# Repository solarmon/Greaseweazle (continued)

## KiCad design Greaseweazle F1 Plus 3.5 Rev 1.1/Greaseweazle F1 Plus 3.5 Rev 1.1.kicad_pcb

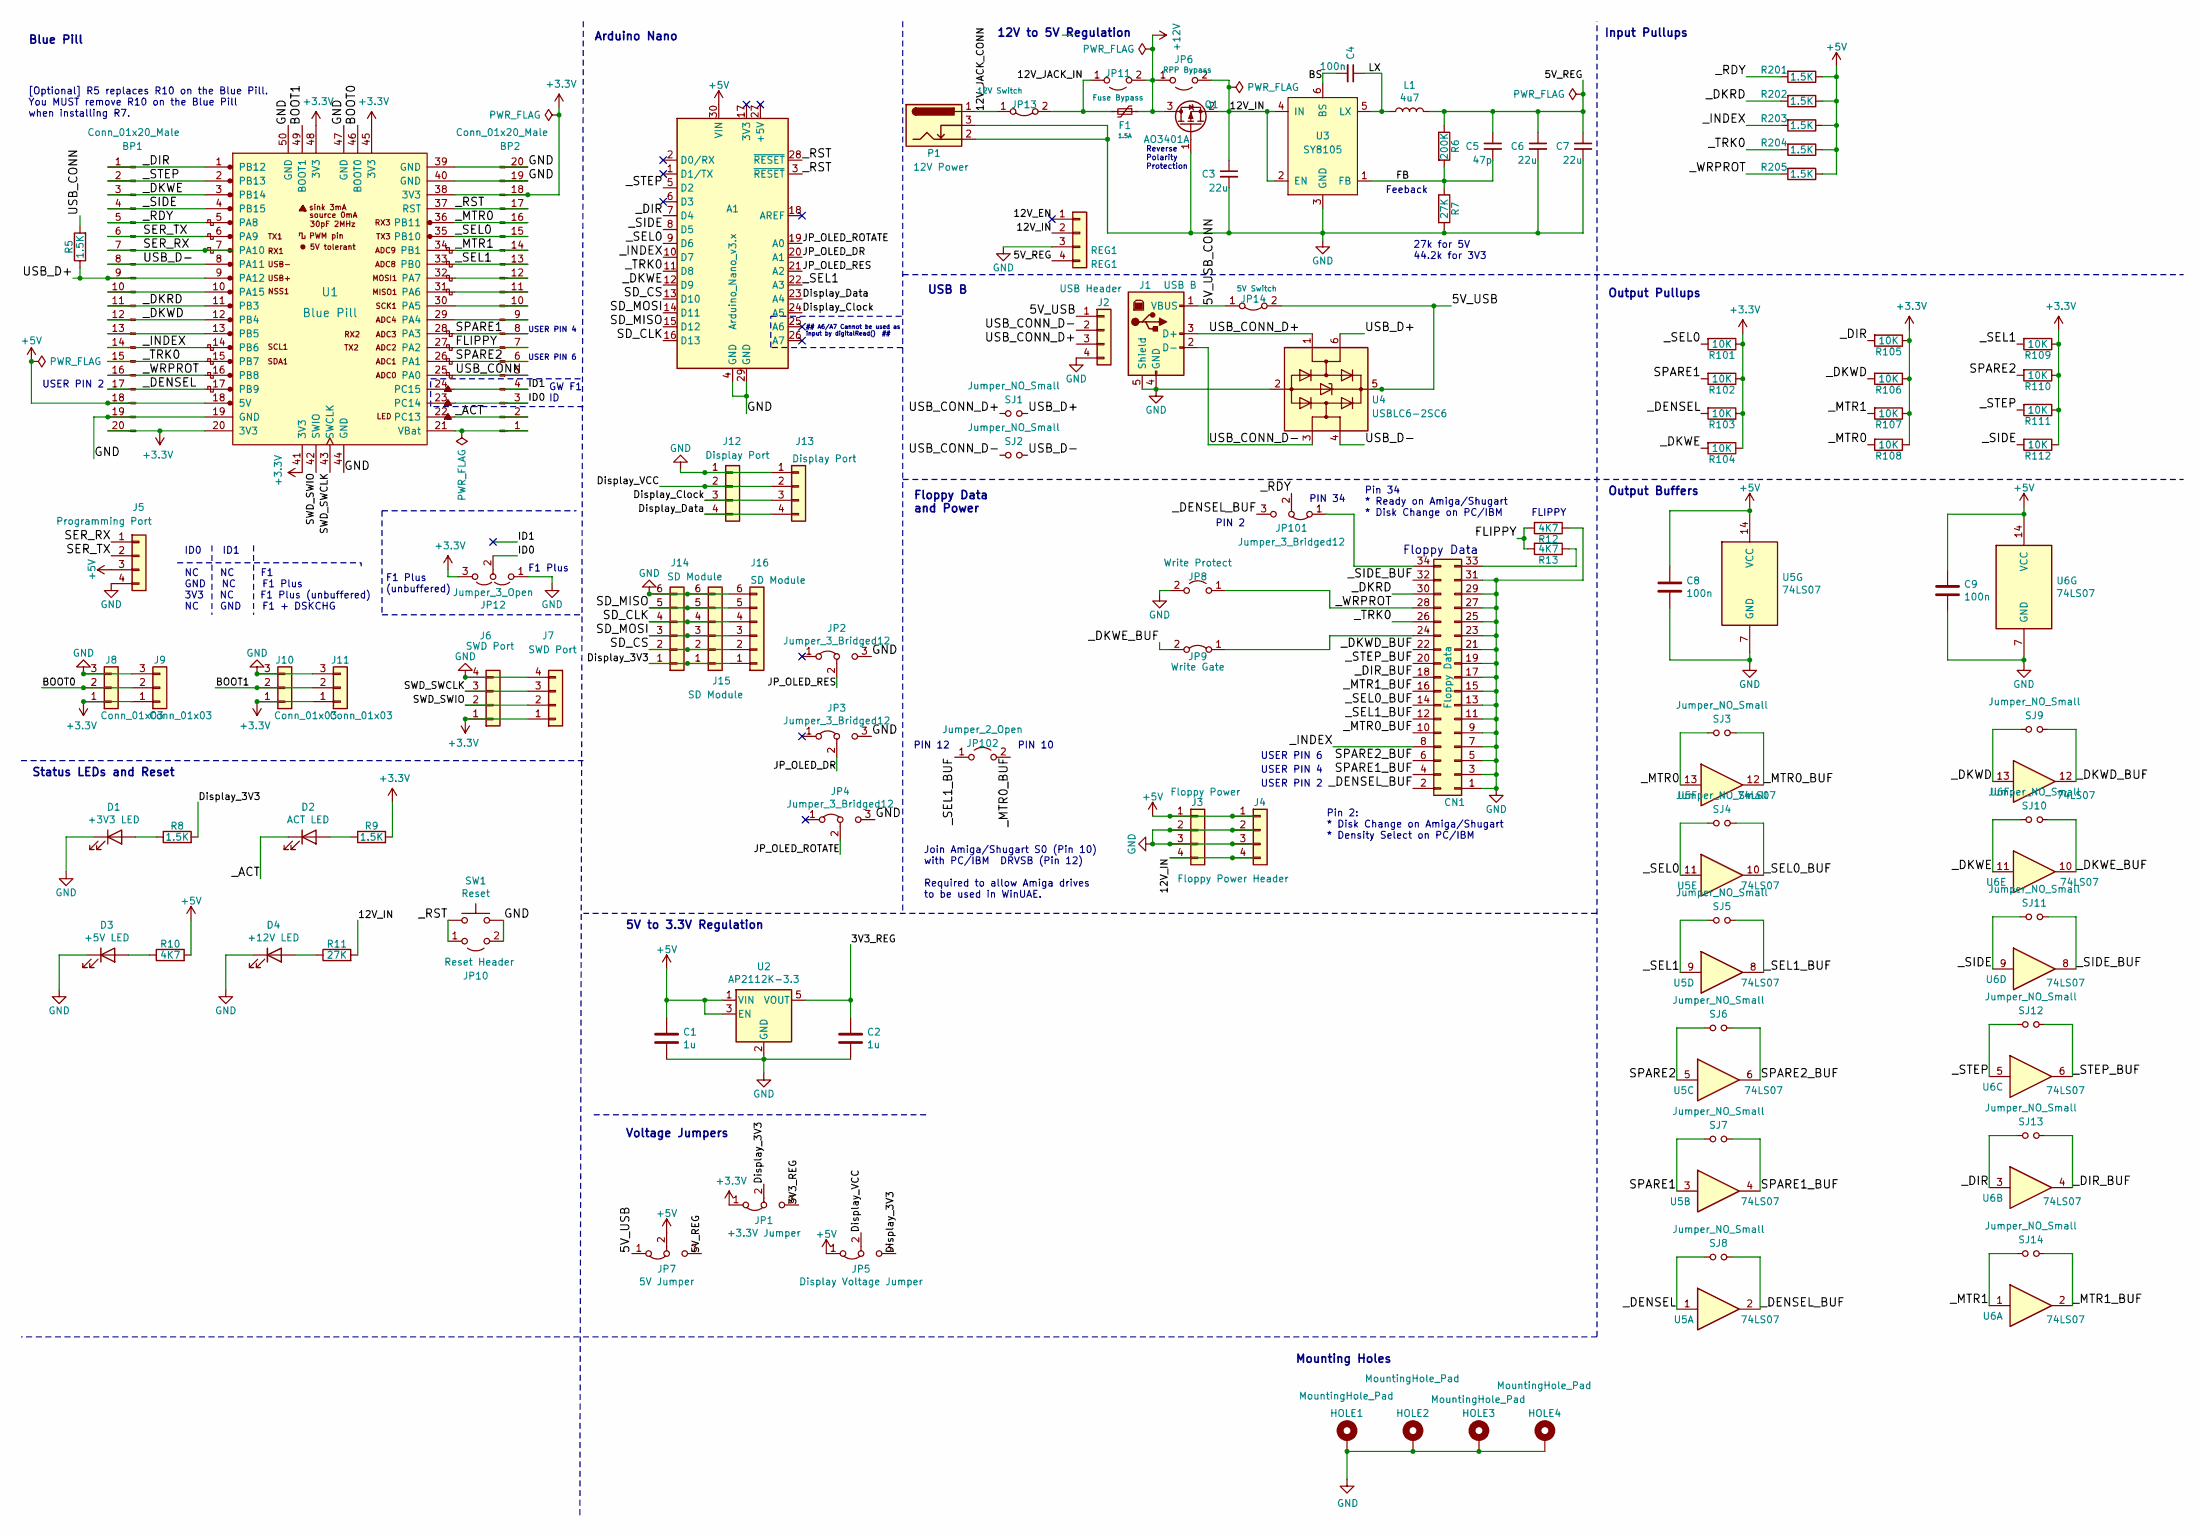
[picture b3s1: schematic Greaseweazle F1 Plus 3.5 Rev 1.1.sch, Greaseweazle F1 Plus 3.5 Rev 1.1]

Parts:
A1: Arduino_Nano_v3.x; Arduino_Nano
BP1, BP2: Conn_01x20_Male; PinHeader_1x20_P2.54mm_Vertical
C1, C2: 1u; C_0805_2012Metric_Pad1.15x1.40mm_HandSolder
C3, C6, C7: 22u; C_0805_2012Metric_Pad1.15x1.40mm_HandSolder
C4, C8, C9: 100n; C_0805_2012Metric_Pad1.15x1.40mm_HandSolder
C5: 47p; C_0805_2012Metric_Pad1.15x1.40mm_HandSolder
CN1: Floppy Data; PinHeader_2x17_P2.54mm_Vertical
D1: +3V3 LED; LED_0805_2012Metric_Pad1.15x1.40mm_HandSolder
D2: ACT LED; LED_0805_2012Metric_Pad1.15x1.40mm_HandSolder
D3: +5V LED; LED_0805_2012Metric_Pad1.15x1.40mm_HandSolder
D4: +12V LED; LED_0805_2012Metric_Pad1.15x1.40mm_HandSolder
F1: 1.5A; Fuse_1206_3216Metric_Pad1.42x1.75mm_HandSolder; LCSC C371166
HOLE1, HOLE2, HOLE3, HOLE4: MountingHole_Pad; HOLE_3MM
J1: USB B; conn_usb_B; LCSC C498173
J2: USB Header; PinHeader_1x04_P2.54mm_Vertical
J3: Floppy Power; PinHeader_1x04_P2.54mm_Horizontal
J4: Floppy Power Header; PinHeader_1x04_P2.54mm_Vertical
J5: Programming Port; PinHeader_1x04_P2.54mm_Horizontal
J6, J7: SWD Port; PinHeader_1x04_P2.54mm_Horizontal
J8, J9, J10, J11: Conn_01x03; PinHeader_1x03_P2.54mm_Horizontal
J12, J13: Display Port; PinHeader_1x04_P2.54mm_Vertical
J14, J15, J16: SD Module; SD_Micro_Module_Upside_Down
JP1: +3.3V Jumper; PinHeader_1x03_P2.54mm_Vertical
JP2, JP3, JP4: Jumper_3_Bridged12; PinHeader_1x03_P2.54mm_Vertical
JP5: Display Voltage Jumper; PinHeader_1x03_P2.54mm_Vertical
JP6: RPP Bypass; PinHeader_1x02_P2.54mm_Vertical
JP7: 5V Jumper; PinHeader_1x03_P2.54mm_Vertical
JP8: Write Protect; PinHeader_1x02_P2.54mm_Horizontal
JP9: Write Gate; PinHeader_1x02_P2.54mm_Horizontal
JP10: Reset Header; PinHeader_1x02_P2.54mm_Vertical
JP11: Fuse Bypass; PinHeader_1x02_P2.54mm_Vertical
JP12: Jumper_3_Open; SolderJumper-3_P1.3mm_Open_RoundedPad1.0x1.5mm
JP13: 12V Switch; PinHeader_1x02_P2.54mm_Vertical
JP14: 5V Switch; PinHeader_1x02_P2.54mm_Vertical
JP101: Jumper_3_Bridged12; PinHeader_1x03_P2.54mm_Horizontal
JP102: Jumper_2_Open; PinHeader_1x02_P2.54mm_Vertical
L1: 4u7; MWSA0503S
P1: 12V Power; BarrelJack_Horizontal; LCSC C16214
Q1: AO3401A; SOT-23_Handsoldering; LCSC C15127
R5, R8, R9, R201, R202, R203, R204, R205: 1.5K; R_0805_2012Metric_Pad1.15x1.40mm_HandSolder
R6: 200K; R_0805_2012Metric_Pad1.15x1.40mm_HandSolder
R7, R11: 27K; R_0805_2012Metric_Pad1.15x1.40mm_HandSolder
R10, R12, R13: 4K7; R_0805_2012Metric_Pad1.15x1.40mm_HandSolder
R101, R102, R103, R104, R105, R106, R107, R108, R109, R110, R111, R112: 10K; R_0805_2012Metric_Pad1.15x1.40mm_HandSolder
REG1: REG1; PinHeader_1x04_P2.54mm_Vertical
SJ1, SJ2, SJ3, SJ4, SJ5, SJ6, SJ7, SJ8, SJ9, SJ10, SJ11, SJ12, SJ13, SJ14: Jumper_NO_Small; SolderJumper-2_Open_RoundedPad0.5x1.0mm
SW1: Reset; PUSH_BUTTON_RIGHT_ANGLE
U1: Blue Pill; YAAJ_BluePill_SWD_1_BootPins
U2: AP2112K-3.3; SOT-23-5_HandSoldering; LCSC C51118
U3: SY8105; TSOT-23-6_HandSoldering; LCSC C178247
U4: USBLC6-2SC6; SOT-23-6_Handsoldering; LCSC C7519
U5, U6: 74LS07; SOIC-14_3.9x8.7mm_P1.27mm; LCSC C513513

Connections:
+3V3: BP1.20, BP2.18, J6.1, J7.1, J8.1, J9.1, J10.1, J11.1, JP1.1 (A), JP12.3 (B), R9.2, R101.1, R102.1, R103.1, R104.1, R105.1, R106.1, R107.1, R108.1, R109.1, R110.1, R111.1, R112.1, U1.20 (3V3), U1.38 (3V3), U1.41 (3V3), U1.45 (3V3), U1.48 (3V3); also elsewhere on the board
+5V: A1.30 (VIN), BP1.18, C1.1, C8.1, C9.1, J3.1, J4.1, J5.3, JP5.1 (A), JP7.2 (C), R10.2, R201.1, R202.1, R203.1, R204.1, R205.1, U1.18 (5V), U2.1 (VIN), U2.3 (EN), U5.14 (VCC), U6.14 (VCC); also elsewhere on the board
+12V: F1.1, JP6.1 (A), JP11.2 (B), Q1.3 (D)
/3V3_REG: C2.1, JP1.3 (B), U2.5 (VOUT)
/5V_REG: C5.1, C6.1, C7.1, JP7.3 (B), L1.2, R6.1, REG1.4
/5V_USB: J2.1, JP7.1 (A), JP14.2 (B), U4.5 (VBUS)
/5V_USB_CONN: J1.1 (VBUS), JP14.1 (A)
/12V_EN: REG1.1
/12V_IN: C3.1, J3.4, J4.4, JP6.2 (B), Q1.2 (S), R11.2, REG1.2, U3.2 (EN), U3.4 (IN); also elsewhere on the board
/12V_JACK_CONN: JP13.1 (A), P1.1
/12V_JACK_IN: F1.2, JP11.1 (A), JP13.2 (B)
/BOOT0: J8.2, J9.2, U1.46 (BOOT0)
/BOOT1: J10.2, J11.2, U1.49 (BOOT1)
/BS: C4.2, U3.6 (BS)
/Display_3V3: J14.1, J15.1, J16.1, JP1.2 (C), JP5.3 (B), R8.2; also elsewhere on the board
/Display_Clock: A1.24 (A5), J12.3, J13.3
/Display_Data: A1.23 (A4), J12.4, J13.4
/Display_VCC: J12.2, J13.2, JP5.2 (C)
/FB: C5.2, R6.2, R7.1, U3.1 (FB)
/FLIPPY: BP2.7, R12.2, R13.2, U1.27 (PA2)
/ID0: BP2.3, JP12.2 (C), U1.23 (PC14)
/ID1: BP2.4, U1.24 (PC15)
/JP_OLED_DR: A1.20 (A1), JP3.2 (C)
/JP_OLED_RES: A1.21 (A2), JP2.2 (C)
/JP_OLED_ROTATE: A1.19 (A0), JP4.2 (C)
/LX: C4.1, L1.1, U3.5 (LX)
/SD_CLK: A1.16 (D13), J14.4, J15.4, J16.4
/SD_CS: A1.13 (D10), J14.2, J15.2, J16.2
/SD_MISO: A1.15 (D12), J14.5, J15.5, J16.5
/SD_MOSI: A1.14 (D11), J14.3, J15.3, J16.3
/SER_RX: BP1.7, J5.1, U1.7 (PA10)
/SER_TX: BP1.6, J5.2, U1.6 (PA9)
/SPARE1: BP2.8, R102.2, SJ7.2, U1.28 (PA3), U5.3
/SPARE1_BUF: CN1.4, SJ7.1, U5.4
/SPARE2: BP2.6, R110.2, SJ6.2, U1.26 (PA1), U5.5
/SPARE2_BUF: CN1.6, SJ6.1, U5.6
/SWD_SWCLK: J6.3, J7.3, U1.43 (SWCLK)
/SWD_SWIO: J6.2, J7.2, U1.42 (SWIO)
/USB_CONN: BP2.5, R5.2, U1.25 (PA0); also elsewhere on the board
/USB_CONN_D+: J1.3 (D+), J2.3, SJ1.2, U4.1 (I/O1)
/USB_CONN_D-: J1.2 (D-), J2.2, SJ2.2, U4.3 (I/O2)
/USB_D+: BP1.9, R5.1, SJ1.1, U1.9 (PA12), U4.6 (I/O1); also elsewhere on the board
/USB_D-: BP1.8, SJ2.1, U1.8 (PA11), U4.4 (I/O2)
/_ACT: BP2.2, D2.1 (K), U1.22 (PC13); also elsewhere on the board
/_DENSEL: BP1.17, R103.2, SJ8.2, U1.17 (PB9), U5.1
/_DENSEL_BUF: CN1.2, JP101.3 (B), SJ8.1, U5.2
/_DIR: A1.7 (D4), BP1.1, R105.2, SJ13.2, U1.1 (PB12), U6.3
/_DIR_BUF: CN1.18, SJ13.1, U6.4
/_DKRD: BP1.11, CN1.30, R202.2, U1.11 (PB3)
/_DKWD: BP1.12, R106.2, SJ9.2, U1.12 (PB4), U6.13
/_DKWD_BUF: CN1.22, SJ9.1, U6.12
/_DKWE: A1.12 (D9), BP1.3, R104.2, SJ10.2, U1.3 (PB14), U6.11
/_DKWE_BUF: JP9.2 (B), SJ10.1, U6.10
/_INDEX: A1.10 (D7), BP1.14, CN1.8, R203.2, U1.14 (PB6)
/_MTR0: BP2.16, R108.2, SJ3.2, U1.36 (PB11), U5.13
/_MTR0_BUF: CN1.10, JP102.2 (B), SJ3.1, U5.12
/_MTR1: BP2.14, R107.2, SJ14.2, U1.34 (PB1), U6.1
/_MTR1_BUF: CN1.16, SJ14.1, U6.2
/_RDY: BP1.5, JP101.2 (C), R201.2, U1.5 (PA8)
/_RST: A1.3 (~RESET), A1.28 (~RESET), BP2.17, JP10.1 (A), SW1.1, U1.37 (RST)
/_SEL0: A1.9 (D6), BP2.15, R101.2, SJ4.2, U1.35 (PB10), U5.11
/_SEL0_BUF: CN1.14, SJ4.1, U5.10
/_SEL1: A1.22 (A3), BP2.13, R109.2, SJ5.2, U1.33 (PB0), U5.9
/_SEL1_BUF: CN1.12, JP102.1 (A), SJ5.1, U5.8
/_SIDE: A1.8 (D5), BP1.4, R112.2, SJ11.2, U1.4 (PB15), U6.9
/_SIDE_BUF: CN1.32, SJ11.1, U6.8
/_STEP: A1.5 (D2), BP1.2, R111.2, SJ12.2, U1.2 (PB13), U6.5
/_STEP_BUF: CN1.20, SJ12.1, U6.6
/_TRK0: A1.11 (D8), BP1.15, CN1.26, R204.2, U1.15 (PB7)
/_WRPROT: BP1.16, CN1.28, JP8.1 (A), R205.2, U1.16 (PB8)
GND: A1.4 (GND), A1.29 (GND), BP1.19, BP2.19, BP2.20, C1.2, C2.2, C3.2, C6.2, C7.2, C8.2, C9.2, CN1.1, CN1.3, CN1.5, CN1.7, CN1.9, CN1.11, CN1.13, CN1.15, CN1.17, CN1.19, CN1.21, CN1.23, CN1.25, CN1.27, CN1.29, CN1.31, D1.1 (K), D3.1 (K), D4.1 (K), HOLE1.1, HOLE2.1, HOLE3.1, HOLE4.1, J1.4 (GND), J1.5 (Shield), J2.4, J3.2, J3.3, J4.2, J4.3, J5.4, J6.4, J7.4, J8.3, J9.3, J10.3, J11.3, J12.1, J13.1, J14.6, J15.6, J16.6, JP2.3 (B), JP3.3 (B), JP4.3 (B), JP8.2 (B), JP10.2 (B), JP12.1 (A), P1.2, P1.3, Q1.1 (G), R7.2, R12.1, REG1.3, SW1.2, U1.19 (GND), U1.39 (GND), U1.40 (GND), U1.44 (GND), U1.47 (GND), U1.50 (GND), U2.2 (GND), U3.3 (GND), U4.2 (GND), U5.7 (GND), U6.7 (GND); also elsewhere on the board
unnamed: BP1.10, U1.10 (PA15)
unnamed: BP1.13, U1.13 (PB5)
unnamed: BP2.1, U1.21 (VBat)
unnamed: BP2.9, U1.29 (PA4)
unnamed: BP2.10, U1.30 (PA5)
unnamed: BP2.11, U1.31 (PA6)
unnamed: BP2.12, U1.32 (PA7)
unnamed: CN1.24, JP9.1 (A)
unnamed: CN1.33, R13.1
unnamed: CN1.34, JP101.1 (A)
unnamed 89: D1.2 (A), R8.1; also elsewhere on the board
unnamed 90: D2.2 (A), R9.1; also elsewhere on the board
unnamed 91: D3.2 (A), R10.1; also elsewhere on the board
unnamed 92: D4.2 (A), R11.1; also elsewhere on the board

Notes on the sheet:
Floppy Data
[Optional] R5 replaces R10 on the Blue Pill. You MUST remove R10 on the Blue Pill when installing R7.
Feeback
27k for 5V 44.2k for 3V3
Reverse Polarity Protection
12V to 5V Regulation
5V to 3.3V Regulation
Floppy Data and Power
Blue Pill
Arduino Nano
Voltage Jumpers
USB B
Mounting Holes
Status LEDs and Reset
GW F1 ID
F1 Plus
FLIPPY
Input Pullups
Output Pullups
Output Buffers
USER PIN 2
USER PIN 4
USER PIN 6
## A6/A7 Cannot be used as input by digitalRead() ##
Join Amiga/Shugart S0 (Pin 10) with PC/IBM DRVSB (Pin 12) Required to allow Amiga drives to be used in WinUAE.
PIN 12
PIN 10
PIN 34
PIN 2
Pin 34 * Ready on Amiga/Shugart * Disk Change on PC/IBM
Pin 2: * Disk Change on Amiga/Shugart * Density Select on PC/IBM
F1 Plus (unbuffered)
ID0 ID1 NC NC F1 GND NC F1 Plus 3V3 NC F1 Plus (unbuffered) NC GND F1 + DSKCHG

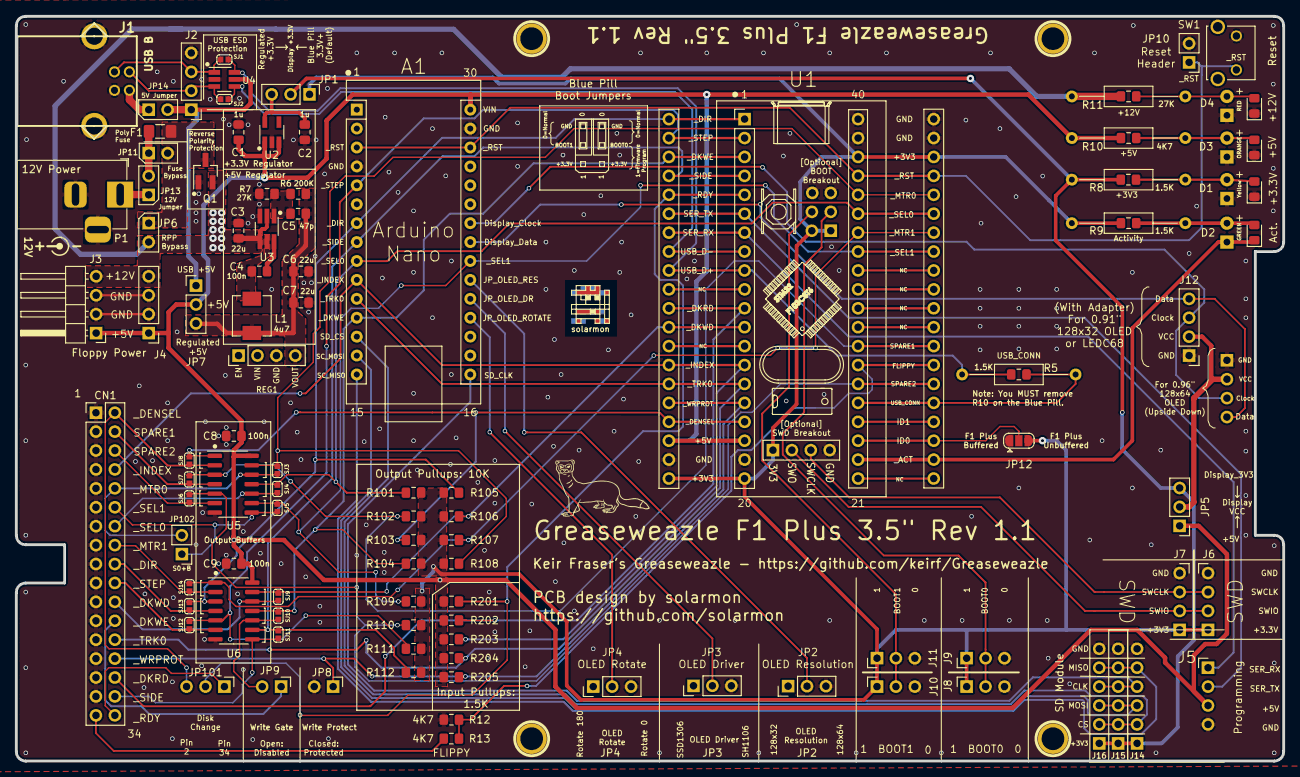
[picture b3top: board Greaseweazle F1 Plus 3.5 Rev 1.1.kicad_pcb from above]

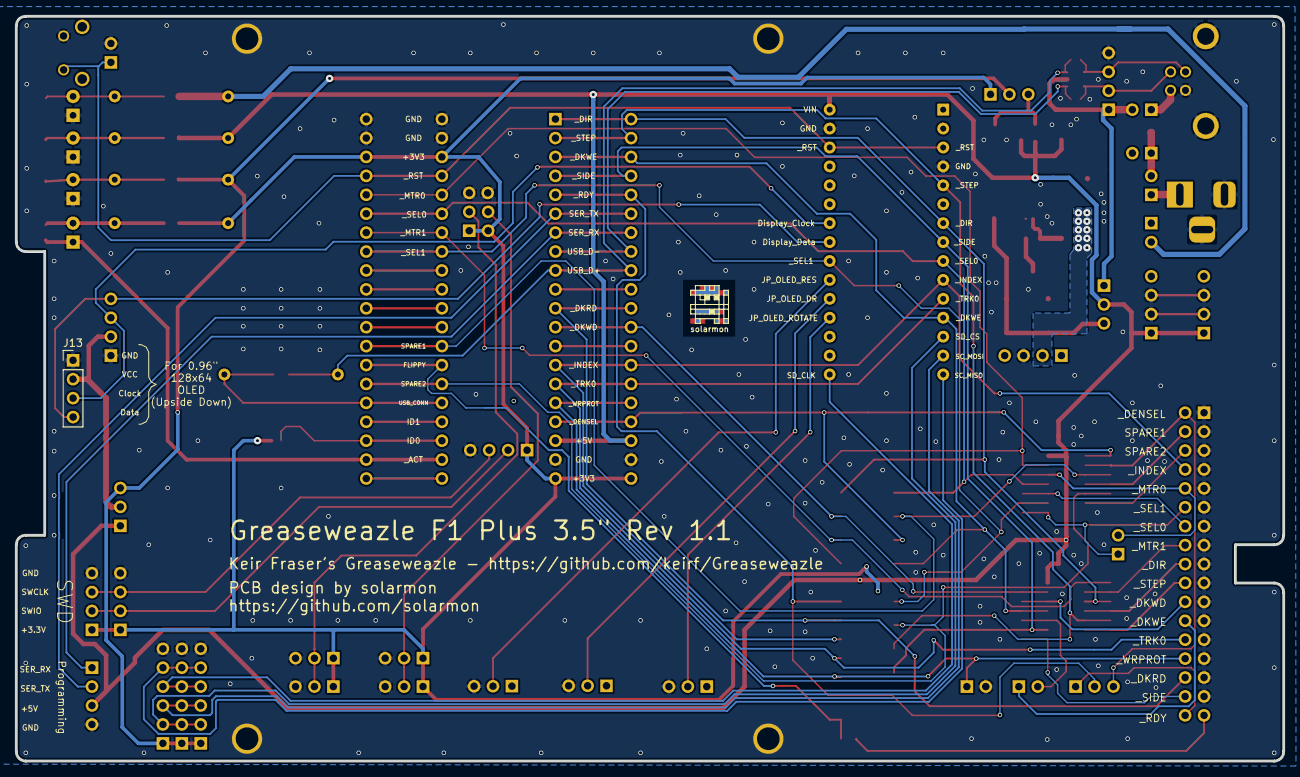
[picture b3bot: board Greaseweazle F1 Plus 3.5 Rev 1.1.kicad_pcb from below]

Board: 2 copper layers, 170.2 x 100.0 mm, 122 parts (2 on the bottom side), 84 nets.

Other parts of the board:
D1#2, D2#2, D3#2: LED_D3.0mm_Horizontal_O1.27mm_Z6.0mm
D4#2: +12V LED; LED_0805_2012Metric_Pad1.15x1.40mm_HandSolder
Floppy Drive: Floppy_Drive
G**: Weasle; WeasleLogo
HEX: Hex_standoff_m3_15mm
HEX#2, HEX#3, HEX#4: Hex_standoff_m3_15mm
R5#2, R8#2, R9#2, R10#2: R_Axial_DIN0207_L6.3mm_D2.5mm_P15.24mm_Horizontal
R11#2: 27K; R_0805_2012Metric_Pad1.15x1.40mm_HandSolder
solarmon: solarmon-logo-25mils
solarmon#2: solarmon-logo-25mils

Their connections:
+3V3: R9#2.2; also elsewhere on the board
+5V: R10#2.2; also elsewhere on the board
/12V_IN: R11#2.2; also elsewhere on the board
/Display_3V3: R8#2.2; also elsewhere on the board
/USB_CONN: R5#2.2; also elsewhere on the board
/USB_D+: R5#2.1; also elsewhere on the board
/_ACT: D2#2.1; also elsewhere on the board
GND: D1#2.1, D3#2.1, D4#2.1; also elsewhere on the board
unnamed 89: D1#2.2, R8#2.1; also elsewhere on the board
unnamed 90: D2#2.2, R9#2.1; also elsewhere on the board
unnamed 91: D3#2.2, R10#2.1; also elsewhere on the board
unnamed 92: D4#2.2, R11#2.1; also elsewhere on the board

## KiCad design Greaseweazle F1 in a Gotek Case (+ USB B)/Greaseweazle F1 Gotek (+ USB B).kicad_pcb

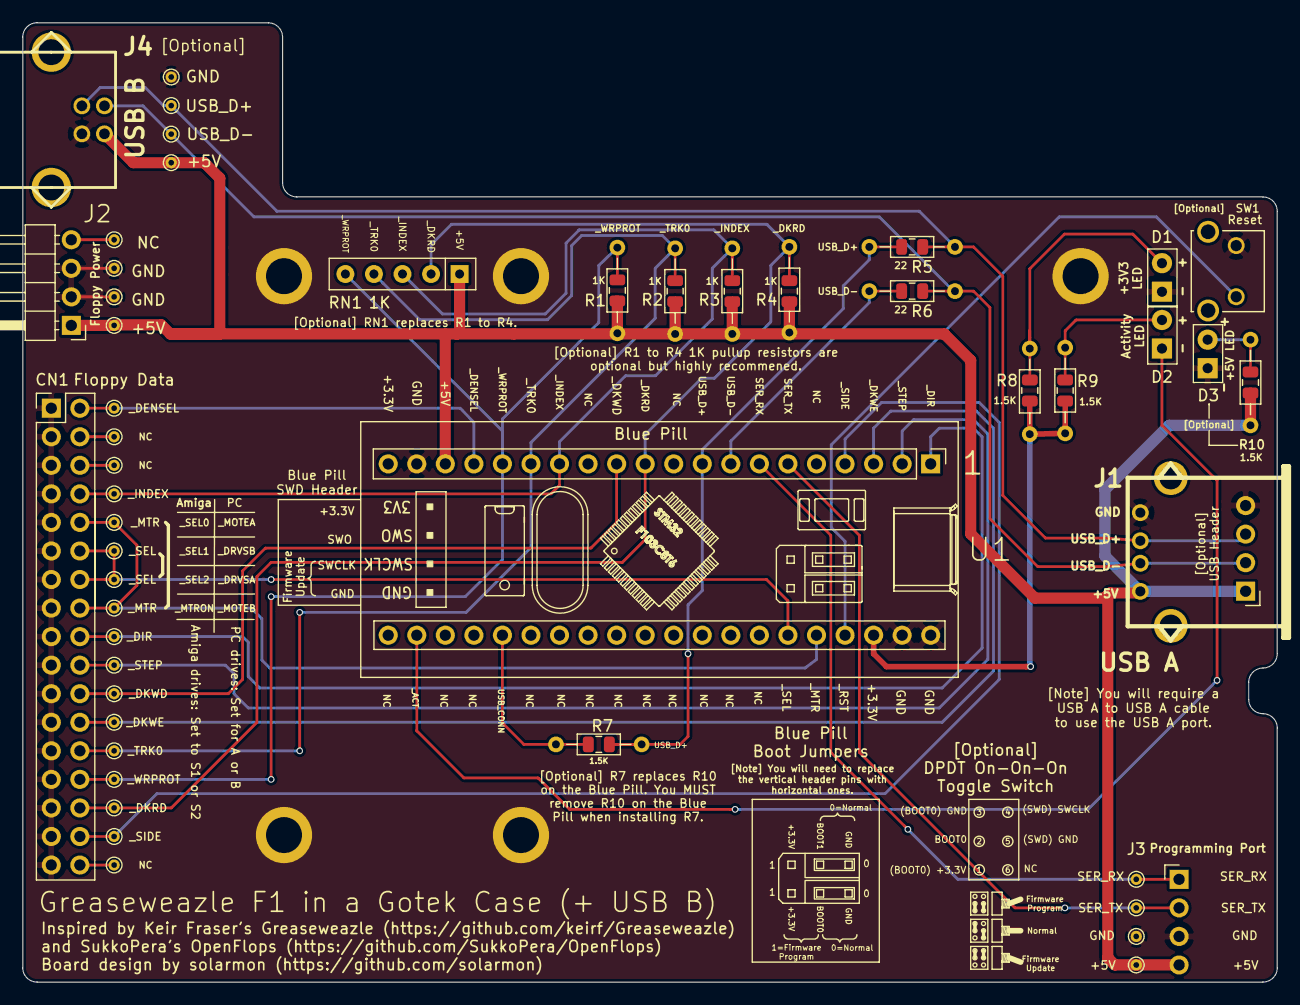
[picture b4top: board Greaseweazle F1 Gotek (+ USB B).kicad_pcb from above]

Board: 2 copper layers, 111.6 x 85.3 mm, 37 parts (0 on the bottom side), 27 nets.

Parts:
CN1: Floppy Data; PinHeader_2x17_P2.54mm_Vertical
D1: +3V3 LED; LED_D3.0mm_Horizontal_O6.35mm_Z10.0mm
D2: ACT LED; LED_D3.0mm_Horizontal_O6.35mm_Z10.0mm
D3: +5V Pwr; LED_D3.0mm_Horizontal_O3.81mm_Z6.0mm
H1, H2, H3, H4, H5: MountingHole_Pad; MountingHole_M3_Pad
J1: USB A; conn_usb_A
J1#2: PinHeader_1x04_P2.54mm_Vertical; PinHeader_1x04_P2.54mm_Horizontal
J2: Floppy Power; PinHeader_1x04_P2.54mm_Horizontal
J3: Programming Port; PinHeader_1x04_P2.54mm_Horizontal
J4: USB B; conn_usb_B
R1, R2, R3, R4, R5, R6, R7, R8, R9, R10: R_Axial_DIN0204_L3.6mm_D1.6mm_P7.62mm_Horizontal
R1#2, R2#2, R3#2, R4#2: 1K; R_0805_2012Metric
R5#2, R6#2: 22; R_0805_2012Metric
R7#2, R8#2, R9#2, R10#2: 1.5K; R_0805_2012Metric
RN1: 1K; R_Array_SIP5
SW1: Reset; PUSH_BUTTON_RIGHT_ANGLE
U1: Blue Pill; YAAJ_BluePill_1

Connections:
+3V3: R8.2, R8#2.2, R9.2, R9#2.2, U1.38
+5V: J1.1, J1#2.1, J2.1, J3.4, J4.1, R1.1, R1#2.1, R2.1, R2#2.1, R3.1, R3#2.1, R4.1, R4#2.1, R10.2, R10#2.2, RN1.1, U1.18
/SER_RX: J3.1, U1.7
/SER_TX: J3.2, U1.6
/USB_CONN: R7.2, R7#2.2, U1.25
/USB_D+: R5.2, R5#2.2, R7.1, R7#2.1, U1.9
/USB_D-: R6.2, R6#2.2, U1.8
/_ACT: D2.1, U1.22
/_DENSEL: CN1.2, U1.17
/_DIR: CN1.18, U1.1
/_DKRD: CN1.30, R4.2, R4#2.2, RN1.2, U1.11
/_DKWD: CN1.22, U1.12
/_DKWE: CN1.24, U1.3
/_INDEX: CN1.8, R3.2, R3#2.2, RN1.3, U1.14
/_MTR: CN1.10, CN1.16, U1.36
/_RST: SW1.1, U1.37
/_SEL: CN1.12, CN1.14, U1.35
/_SIDE: CN1.32, U1.4
/_STEP: CN1.20, U1.2
/_TRK0: CN1.26, R2.2, R2#2.2, RN1.4, U1.15
/_WRPROT: CN1.28, R1.2, R1#2.2, RN1.5, U1.16
GND: CN1.1, CN1.3, CN1.5, CN1.7, CN1.9, CN1.11, CN1.13, CN1.15, CN1.17, CN1.19, CN1.21, CN1.23, CN1.25, CN1.27, CN1.29, CN1.31, CN1.33, D1.1, D3.1, H1.1, H2.1, H3.1, H4.1, H5.1, J1.4, J1#2.4, J2.2, J2.3, J3.3, J4.4, SW1.2, U1.19, U1.39, U1.40
unnamed: D1.2, R8.1, R8#2.1
unnamed: D2.2, R9.1, R9#2.1
unnamed: D3.2, R10.1, R10#2.1
unnamed: J1.2, J1#2.2, J4.2, R6.1, R6#2.1
unnamed: J1.3, J1#2.3, J4.3, R5.1, R5#2.1

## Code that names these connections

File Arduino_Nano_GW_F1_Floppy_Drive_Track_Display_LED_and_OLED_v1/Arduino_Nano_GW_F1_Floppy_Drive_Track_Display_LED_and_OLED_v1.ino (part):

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const byte STEP_Pin = 2;   // D2 (D2 and D3 are interrupt capable)

int DIR_Pin = 4;    // D4
int SIDE_Pin = 5;   // D5
int SEL_Pin = 6;   // D6
int INDEX_Pin = 7;  // D7
int TRK0_Pin = 8;   // D8
int DKWE_Pin = 9;   // D9

int JP_SPARE_Pin = 14;      // D14 / A0
int JP_OLED_DR_Pin = 15;    // D15 / A1
int JP_OLED_RES_Pin = 16;   // D16 / A2


// variables to store the drive signal states
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  // Make interrupt for STEP pin, so that falling edge can be detected.
  pinMode(STEP_Pin, INPUT_PULLUP);
  attachInterrupt(digitalPinToInterrupt(STEP_Pin), stepping, FALLING);
  pinMode(INDEX_Pin, INPUT_PULLUP);
  pinMode(SIDE_Pin, INPUT_PULLUP);
  pinMode(TRK0_Pin, INPUT_PULLUP);
  pinMode(SEL_Pin, INPUT_PULLUP);
  pinMode(DKWE_Pin, INPUT_PULLUP);

  //----------------------------

  // Check Jumpers

  pinMode(JP_SPARE_Pin, INPUT_PULLUP);
  pinMode(JP_OLED_RES_Pin, INPUT_PULLUP);
  pinMode(JP_OLED_DR_Pin, INPUT_PULLUP);

  JP_SPARE_State = digitalRead(JP_SPARE_Pin);
  JP_OLED_RES_State = digitalRead(JP_OLED_RES_Pin);
  JP_OLED_DR_State = digitalRead(JP_OLED_DR_Pin);

  Serial.print(F("### JP_SPARE_State: "));
  Serial.print(JP_SPARE_State);
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          // Poll the drive signals
          DIR_State = digitalRead(DIR_Pin);
          STEP_State = digitalRead(STEP_Pin);
          SIDE_State = digitalRead(SIDE_Pin);
          INDEX_State = digitalRead(INDEX_Pin);
          TRK0_State = digitalRead(TRK0_Pin);
          SEL_State = digitalRead(SEL_Pin); // LOW = STEP IN; HIGH = STEP OUT
          DKWE_State = digitalRead(DKWE_Pin);

          if (TRK0_State == 0)
          {
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
          DIR_State = digitalRead(DIR_Pin);
          STEP_State = digitalRead(STEP_Pin);
          SIDE_State = digitalRead(SIDE_Pin);
          INDEX_State = digitalRead(INDEX_Pin);
          TRK0_State = digitalRead(TRK0_Pin);
          SEL_State = digitalRead(SEL_Pin); // LOW = STEP IN; HIGH = STEP OUT
          DKWE_State = digitalRead(DKWE_Pin);
          
          oled_display.clearDisplay (); // clear display

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
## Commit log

2021-04-10 Added KiCAD design files
2021-05-02 Added Arduino_Nano_GW_F1_Plus_Floppy_Drive_Track_Display_LED_and_OLED
2021-05-13 Added features tables for GW F1 Plus
2021-05-16 Added PNG and PDF files
2021-05-26 Added GW F1 Plus boards - 3.5 and Gotek
2021-05-26 Added images and links about the Gw F1 Plus boards
2021-06-05 Some silk screen updates
2021-06-28 Special thanks to Stefano Cappelli
2021-07-10 Added F1 Plus and F1 Plus Mini
2021-09-22 Added Rev 1.1 versions
2021-09-22 Updated to Rev 1.1 boards
2023-04-02 Corrected image versions
